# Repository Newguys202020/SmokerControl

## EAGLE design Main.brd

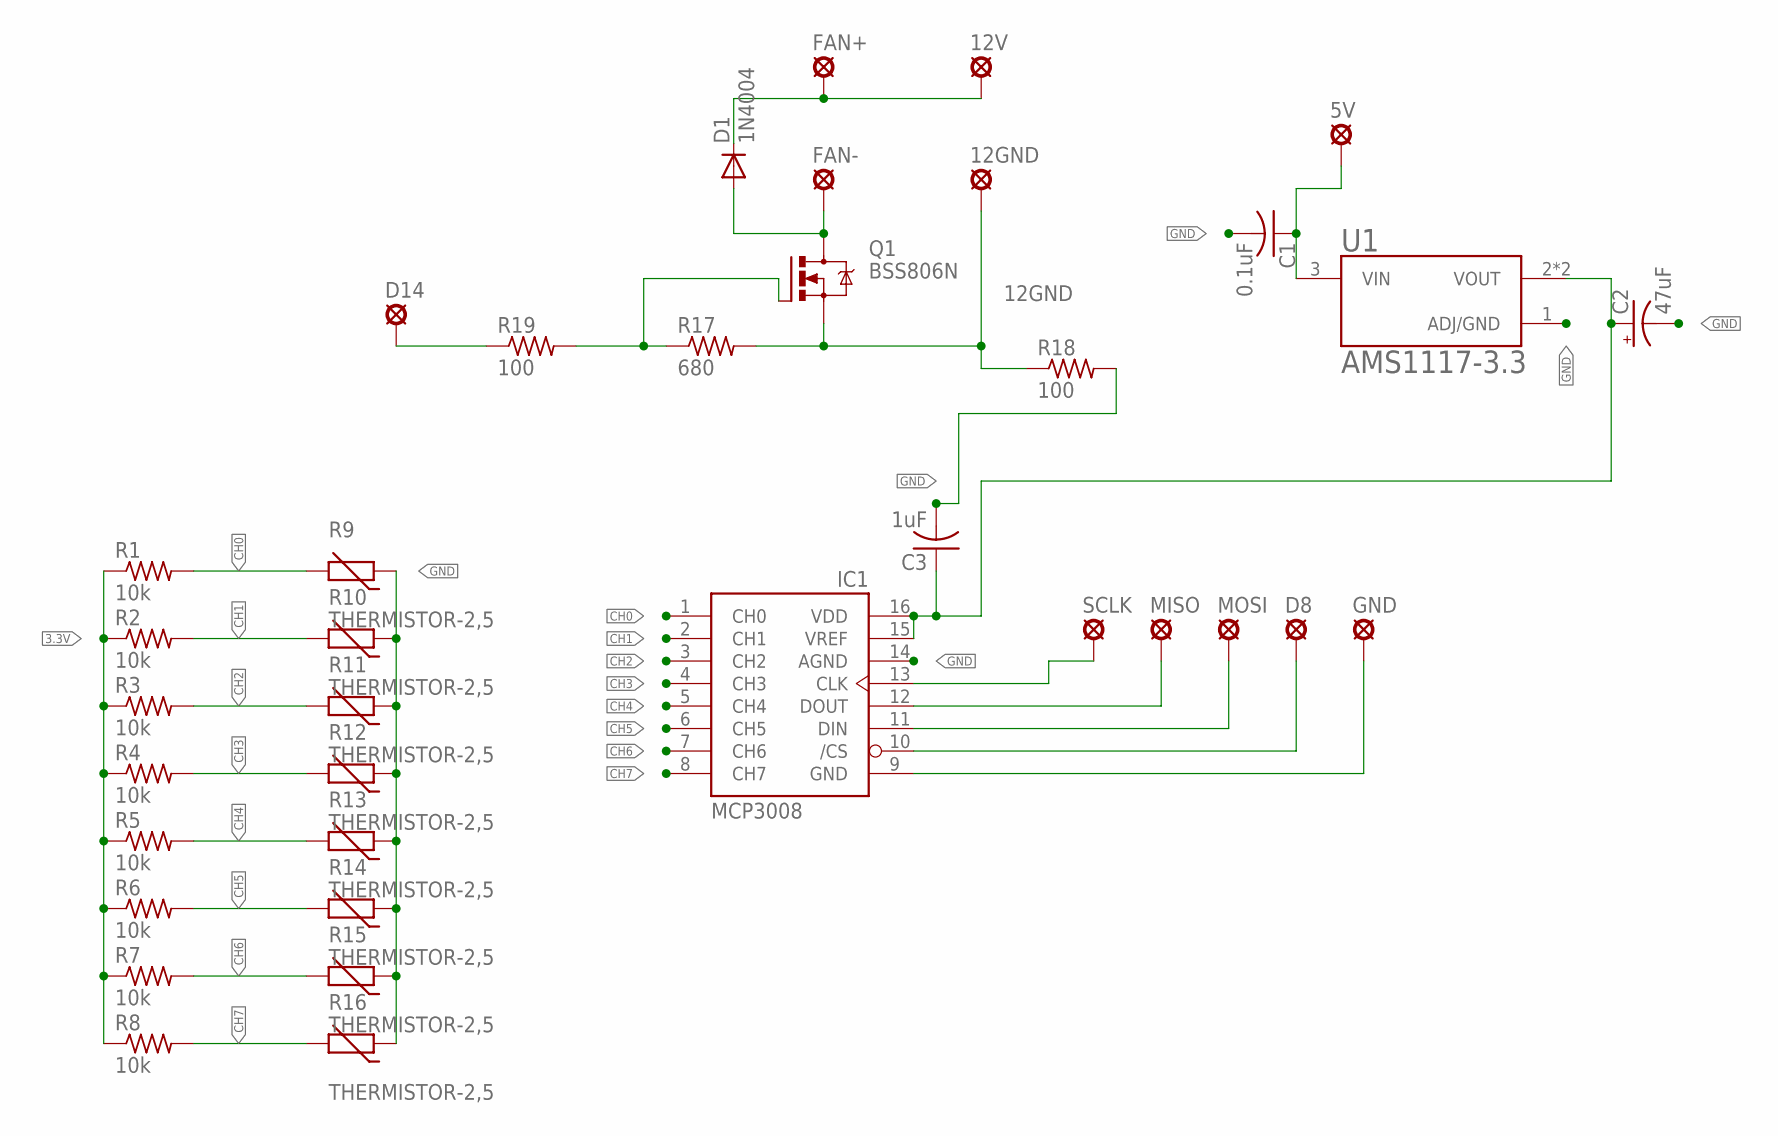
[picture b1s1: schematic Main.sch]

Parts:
5V, 12GND, 12V: LSP10
C1: 0.1uF; C0805
C2: 47uF; E2,5-6
C3: 1uF; C0805
D1: 1N4004; DO41-10
D8, D14: LSP10
FAN+: LSP10
FAN-: LSP10
GND: LSP10
IC1: MCP3008; DIL16
MISO: LSP10
MOSI: LSP10
Q1: BSS806N; SOT23
R1, R2, R3, R4, R5, R6, R7, R8: 10k; R0805
R9, R10, R11, R12, R13, R14, R15, R16: THERMISTOR-2,5; RS-2,5
R17: 680; R0805
R18, R19: 100; R0805
SCLK: LSP10
U1: AMS1117-3.3; SOT229P700X180-4N

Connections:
3.3V: C2.+, C3.1, IC1.15 (VREF), IC1.16 (VDD), R1.1, R2.1, R3.1, R4.1, R5.1, R6.1, R7.1, R8.1, U1.2 (VOUT), U1.4 (VOUT)
5V: 5V.MP, C1.1, U1.3 (VIN)
12GND: 12GND.MP, Q1.2 (S), R17.2, R18.1
CH0: IC1.1 (CH0), R1.2, R9.2
CH1: IC1.2 (CH1), R2.2, R10.2
CH2: IC1.3 (CH2), R3.2, R11.2
CH3: IC1.4 (CH3), R4.2, R12.2
CH4: IC1.5 (CH4), R5.2, R13.2
CH5: IC1.6 (CH5), R6.2, R14.2
CH6: IC1.7 (CH6), R7.2, R15.2
CH7: IC1.8 (CH7), R8.2, R16.2
D8: D8.MP, IC1.10 (/CS)
GND: C1.2, C2.-, C3.2, GND.MP, IC1.9 (GND), IC1.14 (AGND), R9.1, R10.1, R11.1, R12.1, R13.1, R14.1, R15.1, R16.1, R18.2, U1.1 (ADJ/GND)
MISO: IC1.12 (DOUT), MISO.MP
MOSI: IC1.11 (DIN), MOSI.MP
unnamed: 12V.MP, D1.C, FAN+.MP
unnamed: D14.MP, R19.1
unnamed: D1.A, FAN-.MP, Q1.3 (D)
unnamed: Q1.1 (G), R17.1, R19.2
SCLK: IC1.13 (CLK), SCLK.MP

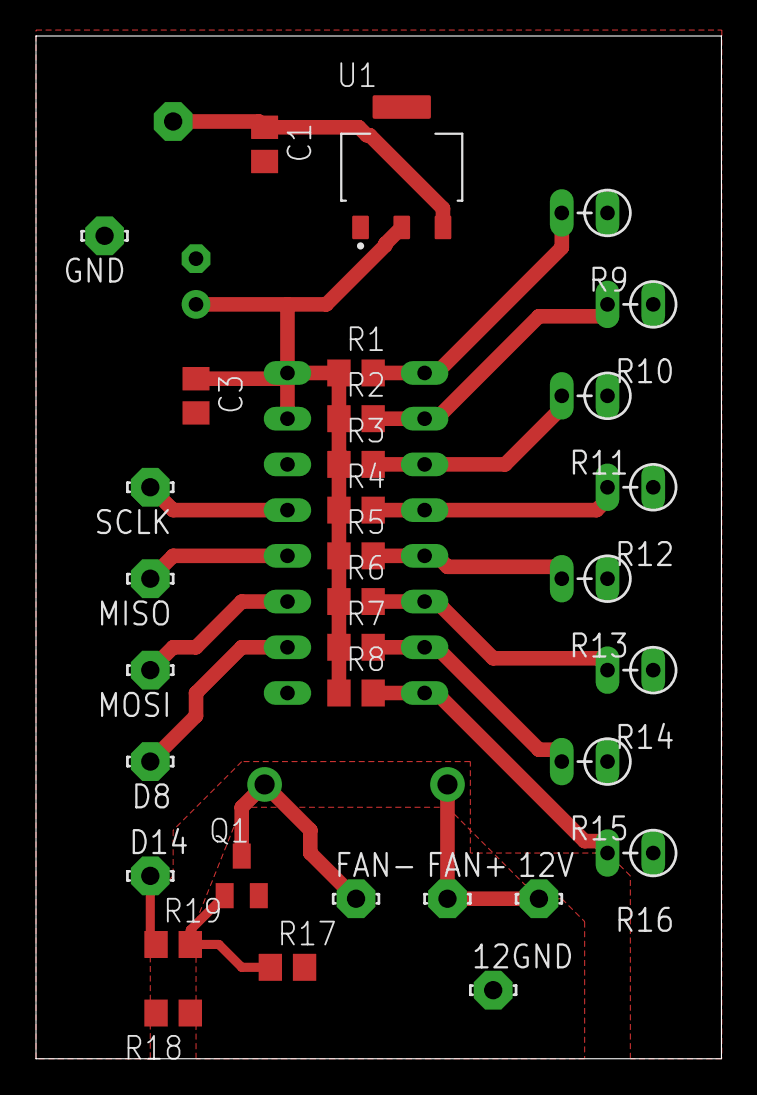
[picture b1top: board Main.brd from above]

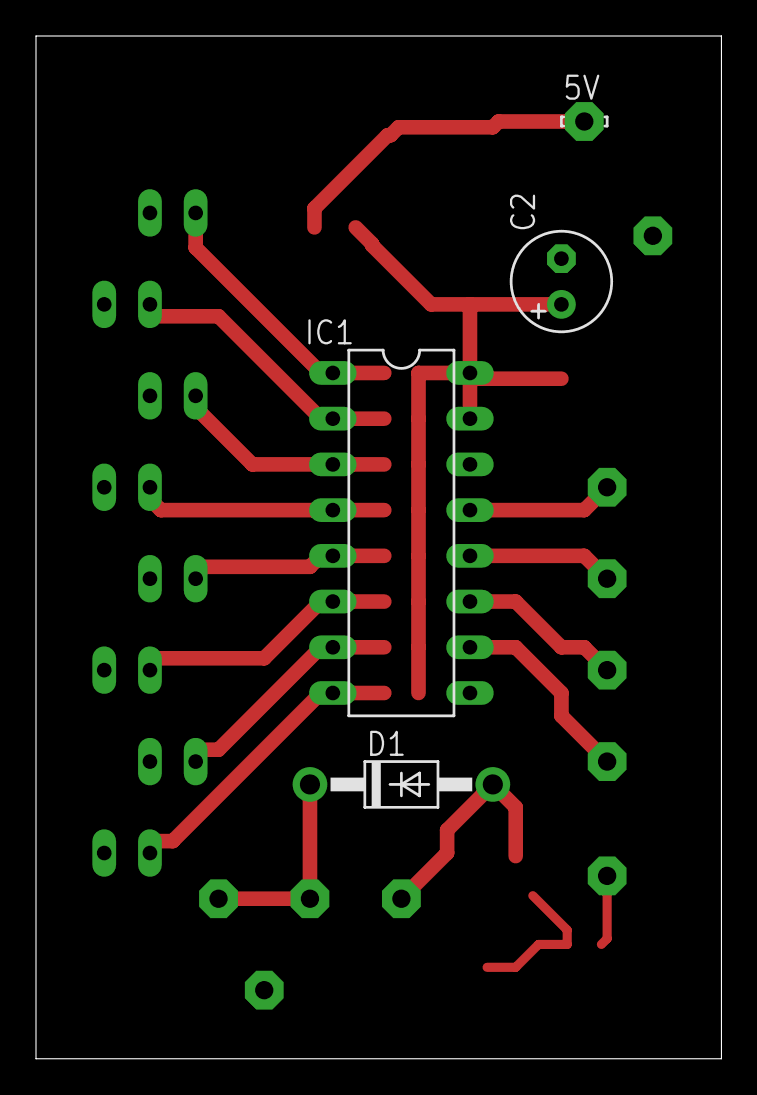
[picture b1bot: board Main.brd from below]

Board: 1 copper layer, 38.1 x 56.8 mm, 37 parts (4 on the bottom side), 20 nets.
